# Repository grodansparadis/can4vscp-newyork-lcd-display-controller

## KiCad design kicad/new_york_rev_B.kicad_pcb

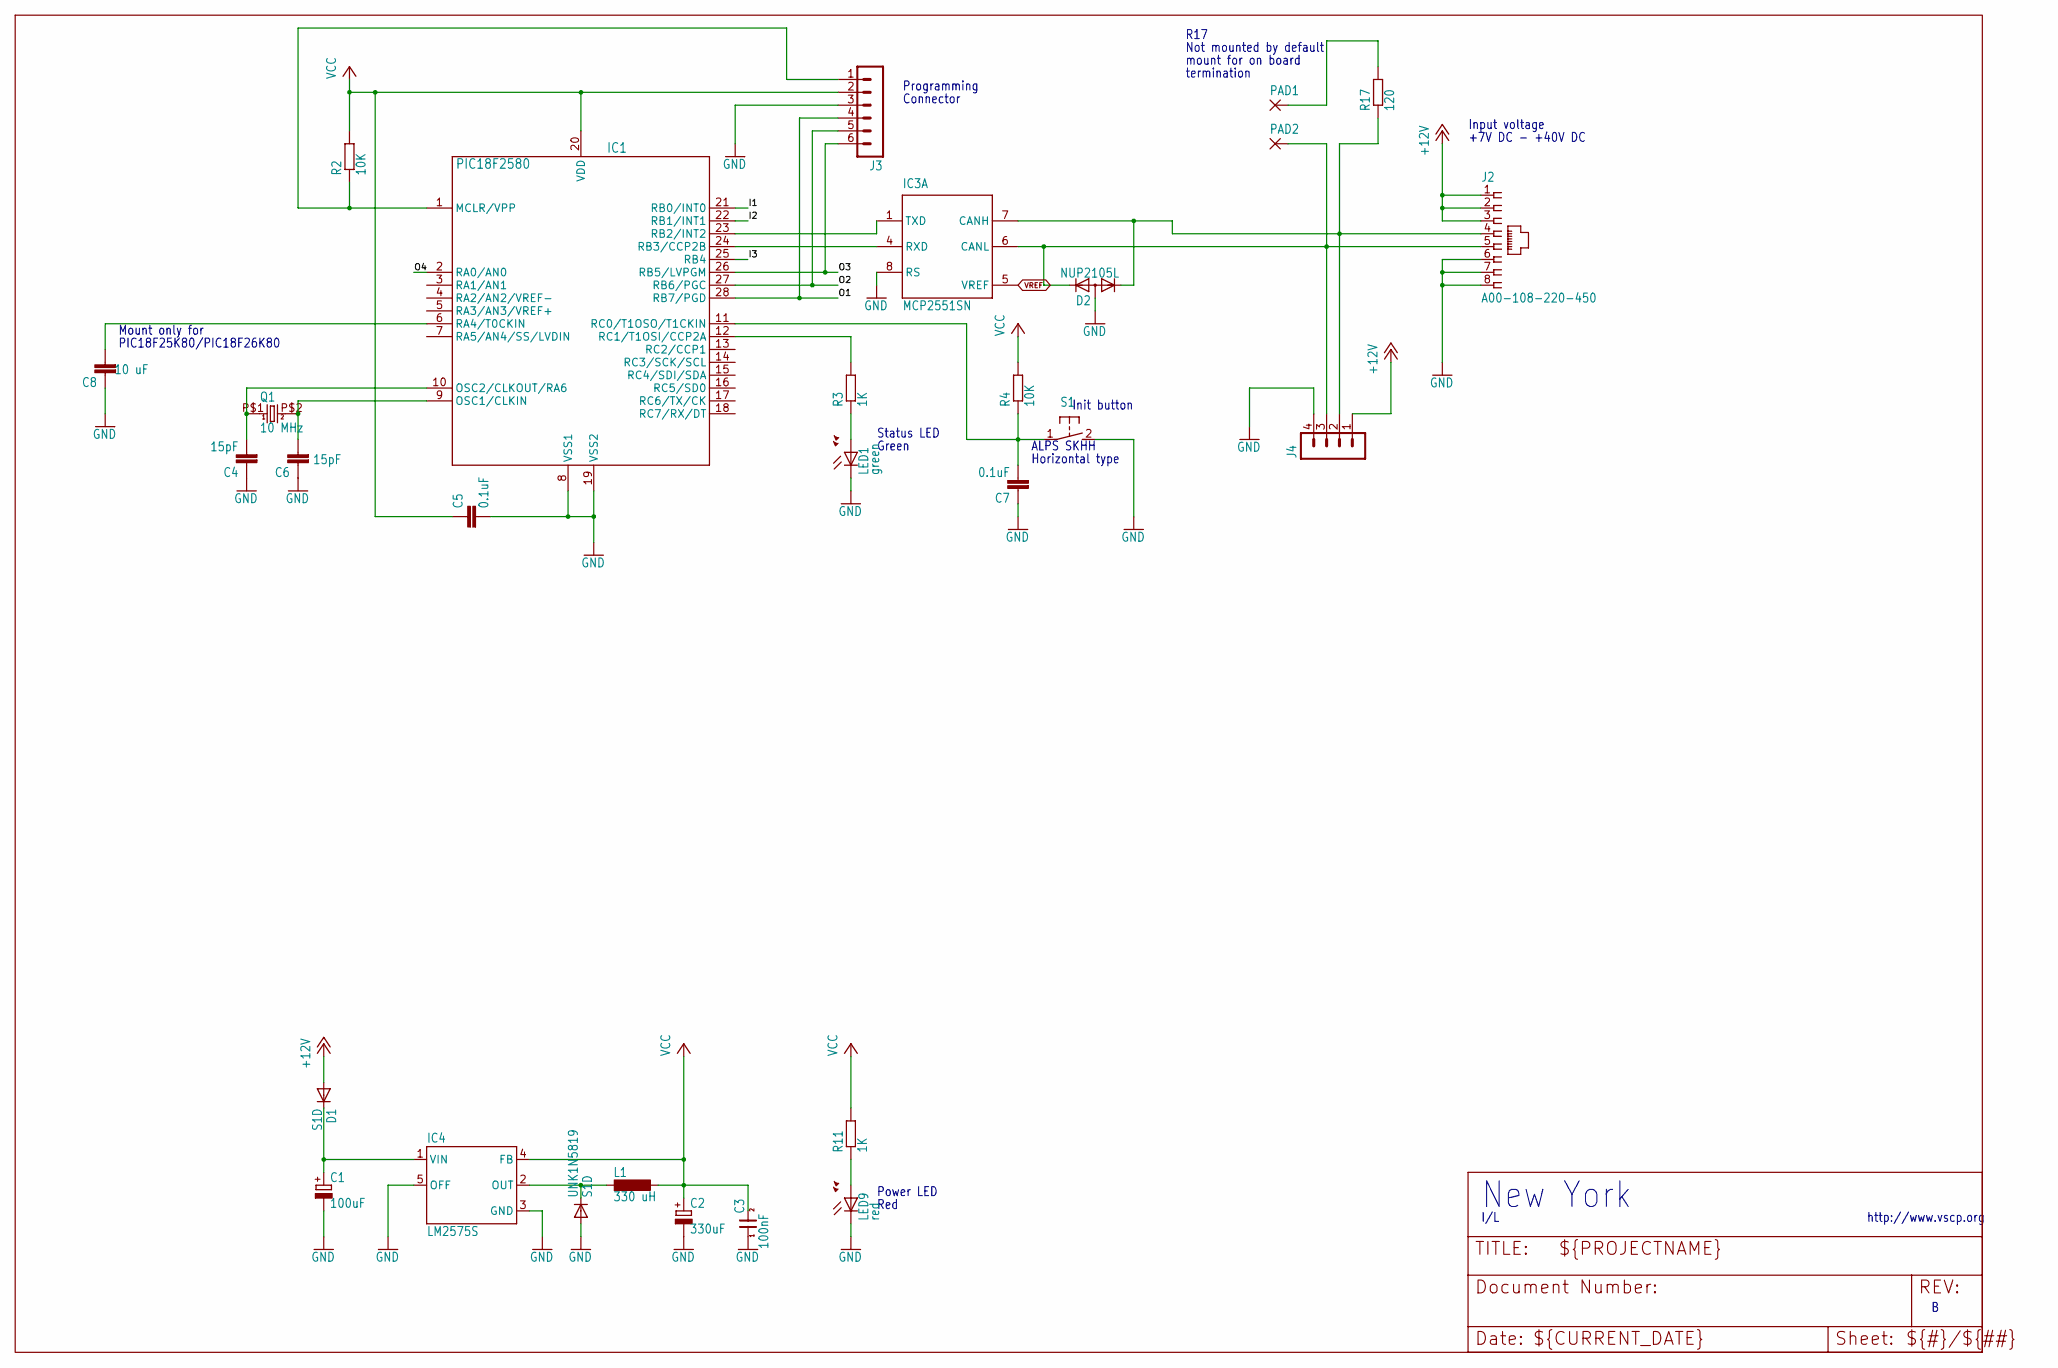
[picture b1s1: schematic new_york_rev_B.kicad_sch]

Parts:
C1: 100uF; PANASONIC_D
C2: 330uF; PANASONIC_D
C3: 100nF; 0805
C4, C6: 15pF; C0805
C5, C7: 0.1uF; C0805
C8: 10 uF; C0805
D1: S1D; SOD123
D2: NUP2105L; SOT23
IC1: PIC18F2580; SO28
IC3: MCP2551SN; SO-08
IC4: LM2575S; TO263-5
J2: A00-108-220-450; RJ-45
J3: MA06-1
J4: MA04-1
L1: 330 uH; DO3316P
LED1: green; CHIP-LED0805
LED9: red; CHIP-LED0805
PAD1, PAD2: 1,6/0,8; 1,6_0,8
Q1: 10 MHz; 9C
R2, R4: 10K; R0805
R3, R11: 1K; R0805
R17: 120; R0805
S1: 31-XX; B3F-31XX
UNK1N5819: S1D; SOD123

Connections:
+12V: D1.A, J2.1, J2.2, J2.3, J4.1
CANL: D2.2 (K2), IC3.6 (CANL), J2.5, J4.3, PAD2.1
GND: C1.-, C2.-, C3.1, C4.1, C5.2, C6.1, C7.1, C8.1, D2.3 (A), IC1.8 (VSS1), IC1.19 (VSS2), IC3.2 (VSS), IC3.8 (RS), IC4.3 (GND), IC4.5 (OFF), J2.6, J2.7, J2.8, J3.3, J4.4, LED1.C, LED9.C, S1.2 (S), UNK1N5819.A
I1: IC1.21 (RB0/INT0)
I2: IC1.22 (RB1/INT1)
I3: IC1.25 (RB4)
unnamed: IC4.2 (OUT), L1.1, UNK1N5819.C
unnamed: C4.2, IC1.10 (OSC2/CLKOUT/RA6), Q1.P$1 (1)
unnamed: C1.+, D1.C, IC4.1 (VIN)
unnamed: IC1.12 (RC1/T1OSI/CCP2A), R3.2
unnamed: LED1.A, R3.1
unnamed: C7.2, IC1.11 (RC0/T1OSO/T1CKIN), R4.1, S1.1
unnamed: C6.2, IC1.9 (OSC1/CLKIN), Q1.P$2 (2)
unnamed: IC1.1 (MCLR/VPP), J3.1, R2.1
unnamed: LED9.A, R11.1
unnamed: C8.2, IC1.6 (RA4/T0CKIN)
unnamed: D2.1 (K1), IC3.7 (CANH), J2.4, J4.2, R17.1
unnamed: PAD1.1, R17.2
O1: IC1.28 (RB7/PGD), J3.4
O2: IC1.27 (RB6/PGC), J3.5
O3: IC1.26 (RB5/LVPGM), J3.6
O4: IC1.2 (RA0/AN0)
RXCAN: IC1.24 (RB3/CCP2B), IC3.4 (RXD)
TXCAN: IC1.23 (RB2/INT2), IC3.1 (TXD)
VCC: C2.+, C3.2, C5.1, IC1.20 (VDD), IC3.3 (VDD), IC4.4 (FB), J3.2, L1.2, R2.2, R4.2, R11.2
VREF: IC3.5 (VREF)

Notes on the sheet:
Status LED
Mount only for
I/L
PIC18F25K80/PIC18F26K80
New York
Horizontal type
Input voltage
termination
Not mounted by default
ALPS SKHH
+7V DC - +40V DC
R17
Connector
Green
http://www.vscp.org
Init button
Programming
Power LED
mount for on board
Red

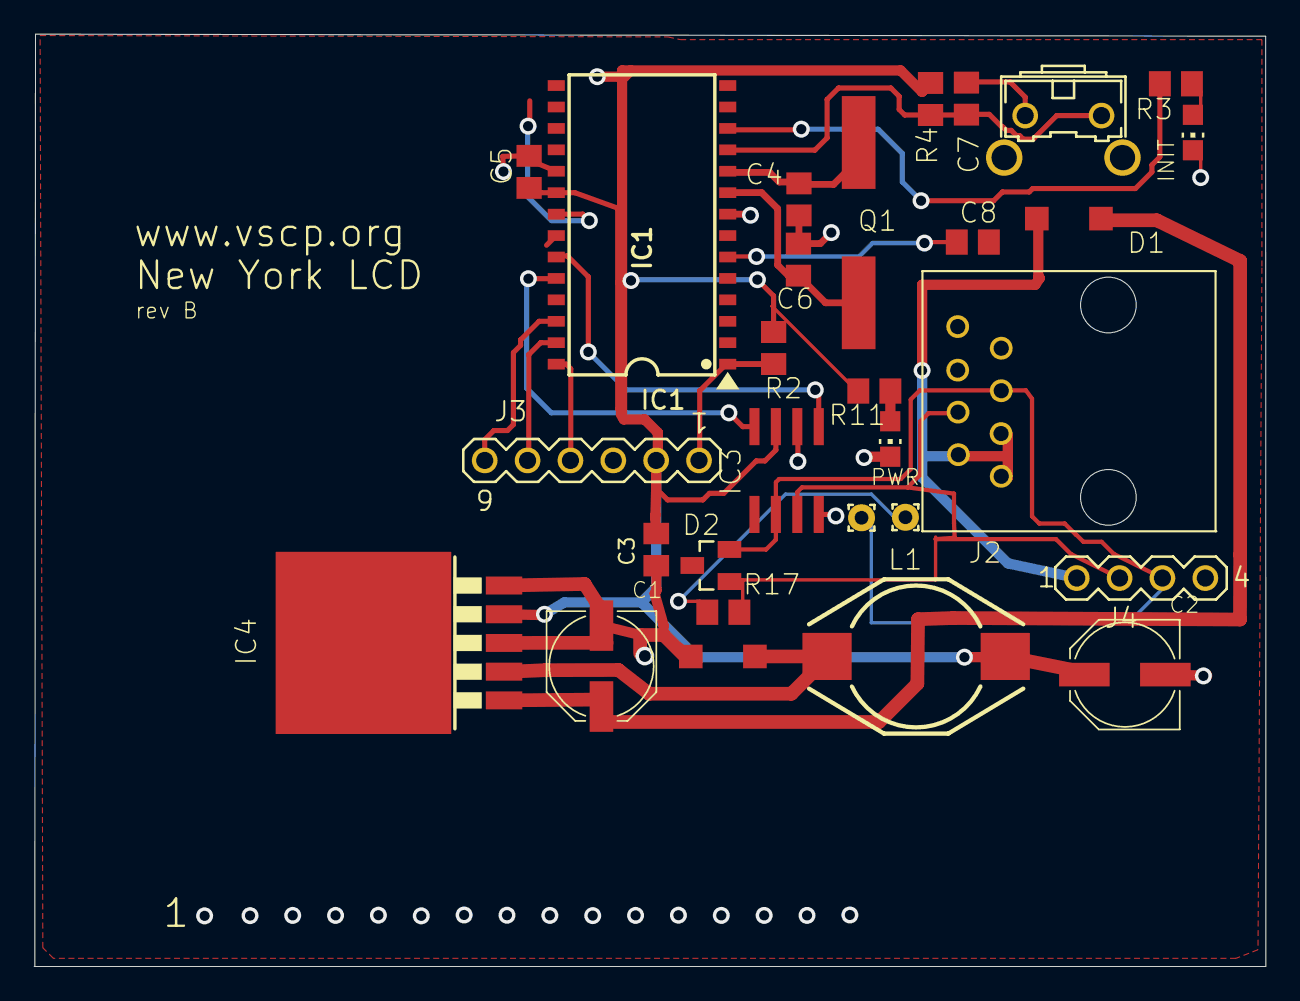
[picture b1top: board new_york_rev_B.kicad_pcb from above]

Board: 6 copper layers, 73.0 x 55.2 mm, 29 parts (0 on the bottom side), 21 nets.

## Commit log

2025-08-18 Converted schema to kicad
2025-09-30 Changed license to MIT
2026-05-05 Updated license to CERN
